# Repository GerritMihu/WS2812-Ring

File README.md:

# WS2812-Ring
 Ledring with the WS2812 RGB LEDs.

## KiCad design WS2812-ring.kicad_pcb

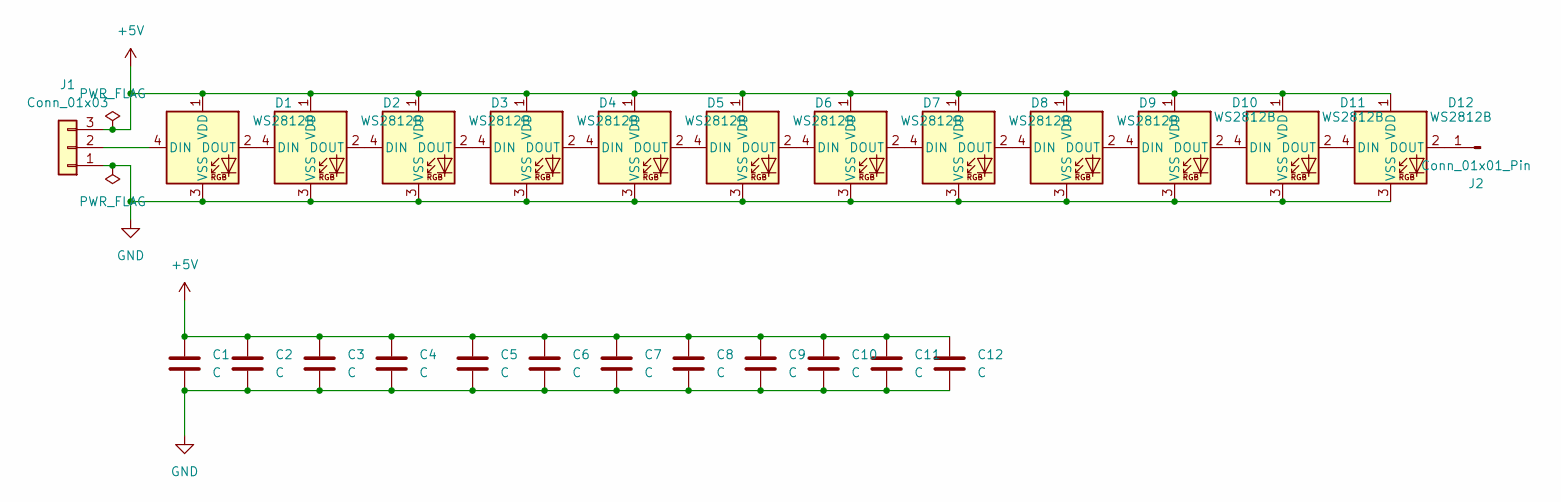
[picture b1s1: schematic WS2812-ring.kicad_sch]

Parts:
C1, C2, C3, C4, C5, C6, C7, C8, C9, C10, C11, C12: C; C_0805_2012Metric_Pad1.18x1.45mm_HandSolder
D1, D2, D3, D4, D5, D6, D7, D8, D9, D10, D11, D12: WS2812B; LED_WS2812B_PLCC4_5.0x5.0mm_P3.2mm
J1: Conn_01x03; PinHeader_1x03_P2.54mm_Vertical; Part Number 1-0301FBV0T
J2: Conn_01x01_Pin; PinHeader_1x01_P2.54mm_Vertical

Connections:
+5V: C1.1, C2.1, C3.1, C4.1, C5.1, C6.1, C7.1, C8.1, C9.1, C10.1, C11.1, C12.1, D1.1 (VDD), D2.1 (VDD), D3.1 (VDD), D4.1 (VDD), D5.1 (VDD), D6.1 (VDD), D7.1 (VDD), D8.1 (VDD), D9.1 (VDD), D10.1 (VDD), D11.1 (VDD), D12.1 (VDD), J1.3
GND: C1.2, C2.2, C3.2, C4.2, C5.2, C6.2, C7.2, C8.2, C9.2, C10.2, C11.2, C12.2, D1.3 (VSS), D2.3 (VSS), D3.3 (VSS), D4.3 (VSS), D5.3 (VSS), D6.3 (VSS), D7.3 (VSS), D8.3 (VSS), D9.3 (VSS), D10.3 (VSS), D11.3 (VSS), D12.3 (VSS), J1.1
unnamed: D1.4 (DIN), J1.2
unnamed: D1.2 (DOUT), D2.4 (DIN)
unnamed: D2.2 (DOUT), D3.4 (DIN)
unnamed: D3.2 (DOUT), D4.4 (DIN)
unnamed: D4.2 (DOUT), D5.4 (DIN)
unnamed: D5.2 (DOUT), D6.4 (DIN)
unnamed: D6.2 (DOUT), D7.4 (DIN)
unnamed: D7.2 (DOUT), D8.4 (DIN)
unnamed: D8.2 (DOUT), D9.4 (DIN)
unnamed: D9.2 (DOUT), D10.4 (DIN)
unnamed: D10.2 (DOUT), D11.4 (DIN)
unnamed: D11.2 (DOUT), D12.4 (DIN)
unnamed: D12.2 (DOUT), J2.1

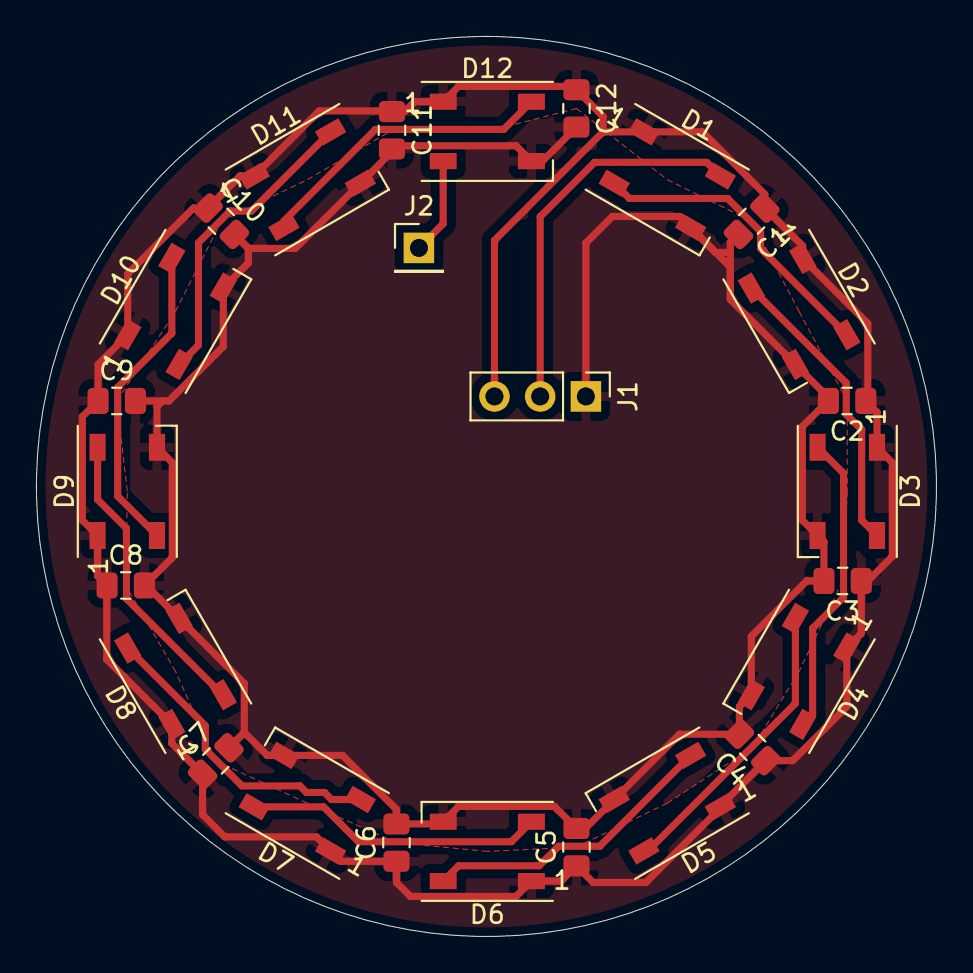
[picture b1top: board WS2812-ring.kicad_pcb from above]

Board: 2 copper layers, 50.0 x 50.0 mm, 26 parts (0 on the bottom side), 15 nets.

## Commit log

2024-04-17 Upload project
